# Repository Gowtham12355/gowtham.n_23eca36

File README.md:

View this project on [CADLAB.io](https://cadlab.io/project/29069). 

# gowtham.n_23eca36

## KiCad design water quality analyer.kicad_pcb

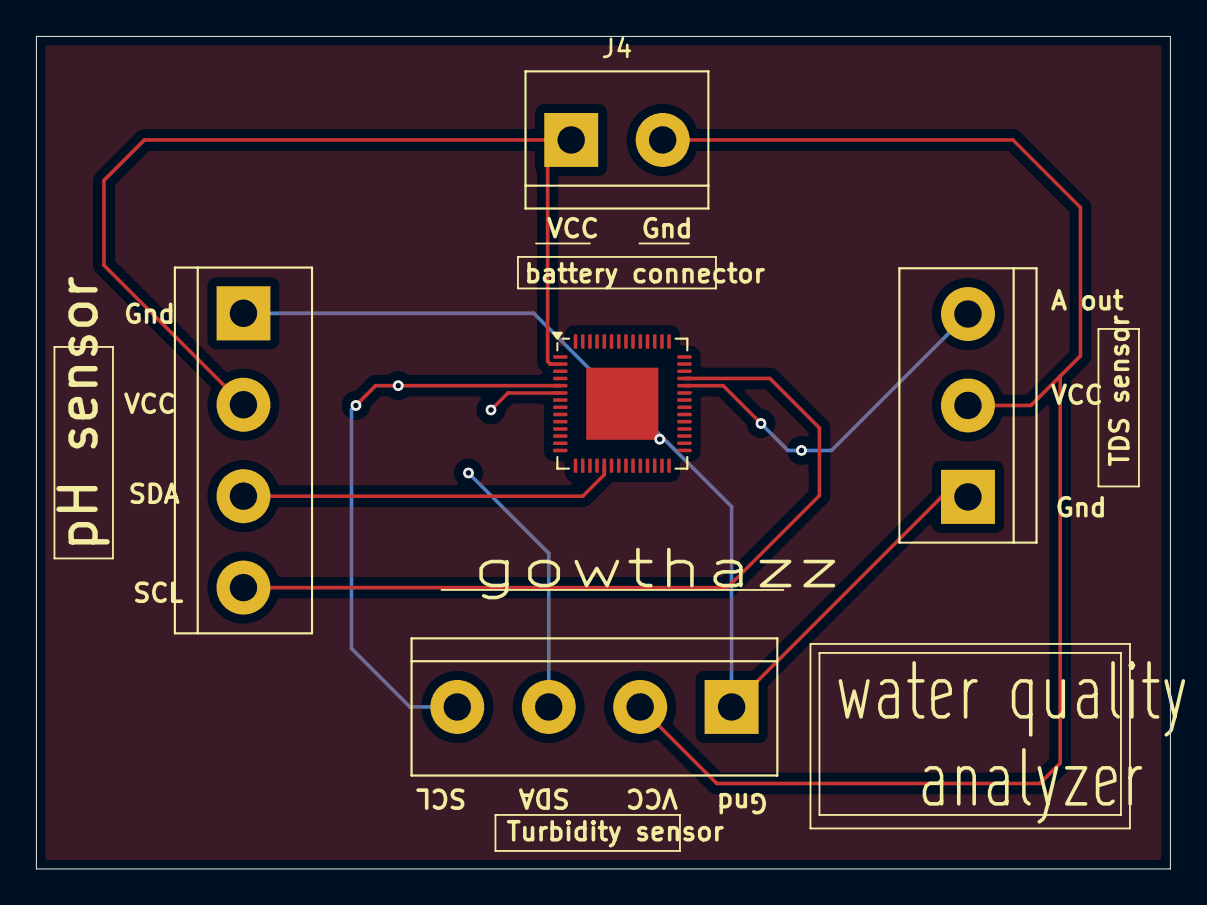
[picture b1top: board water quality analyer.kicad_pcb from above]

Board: 2 copper layers, 63.0 x 46.2 mm, 5 parts (0 on the bottom side), 7 nets.

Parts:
J1: Conn_01x03_Pin; TerminalBlock_bornier-3_P5.08mm
J2, J3: Conn_01x04_Socket; TerminalBlock_bornier-4_P5.08mm
J4: Conn_01x02_Pin; TerminalBlock_bornier-2_P5.08mm
U1: ESP32-S2; QFN-56-1EP_7x7mm_P0.4mm_EP4x4mm

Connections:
unnamed: J1.1, J2.1, J3.1, U1.57 (GND)
unnamed: J1.2, J2.2, J3.2, J4.1, J4.2, U1.2 (LNA_IN)
unnamed: J1.3, U1.38 (GPIO34)
unnamed: J2.3, U1.19 (GPIO14)
unnamed: J2.4, U1.39 (GPIO35)
unnamed: J3.3, U1.6 (GPIO1)
unnamed: J3.4, U1.5 (GPIO0)

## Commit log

2025-03-30 Backlink to CADLAB.io has been added.
